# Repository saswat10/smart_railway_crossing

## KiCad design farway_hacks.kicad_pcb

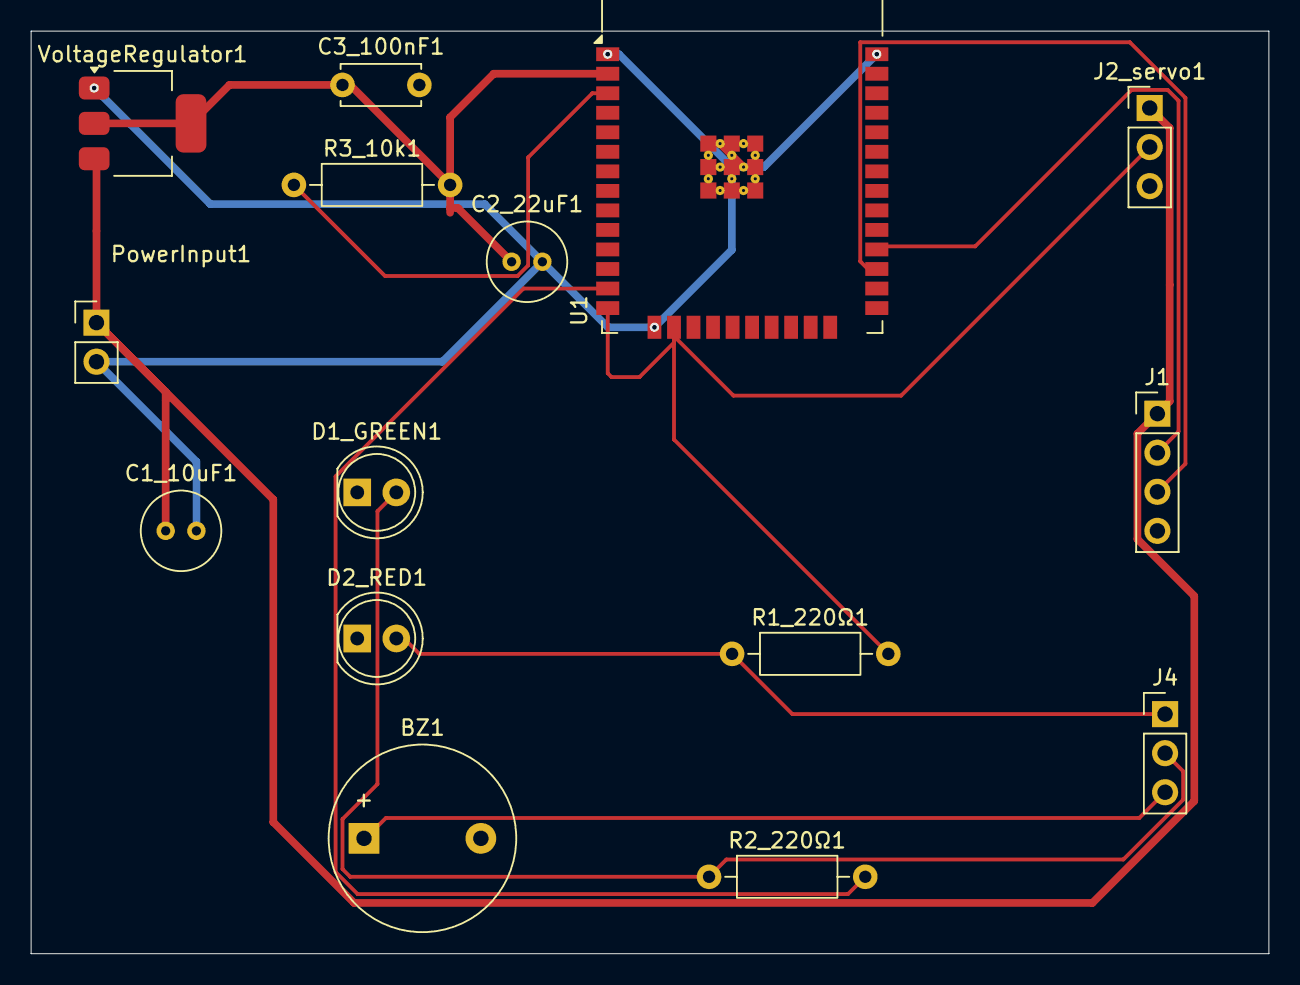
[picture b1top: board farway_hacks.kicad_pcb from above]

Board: 2 copper layers, 80.5 x 60.0 mm, 15 parts (0 on the bottom side), 11 nets.

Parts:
BZ1: Buzzer; Buzzer_12x9.5RM7.6
C1_10uF1, C2_22uF1: 52; C_Radial_D5.0mm_H5.0mm_P2.00mm
C3_100nF1: 52; C_Disc_D5.0mm_W2.5mm_P5.00mm
D1_GREEN1, D2_RED1: LED; LED_D5.0mm
J1: Conn_01x04; PinHeader_1x04_P2.54mm_Vertical
J2_servo1, J4: Conn_01x03; PinHeader_1x03_P2.54mm_Vertical
PowerInput1: Conn_01x02; PinHeader_1x02_P2.54mm_Vertical
R1_220Ω1, R2_220Ω1, R3_10k1: R; R_Axial_DIN0207_L6.3mm_D2.5mm_P10.16mm_Horizontal
U1: ESP32-WROOM-32
VoltageRegulator1: AMS1117-3.3; SOT-223-3_TabPin2

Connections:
+3V3: C2_22uF1.1, C3_100nF1.1, R3_10k1.2, U1.2 (VDD), VoltageRegulator1.2 (VO)
+5V: C1_10uF1.1, J1.1, J2_servo1.1, PowerInput1.1, VoltageRegulator1.3 (VI)
GND: BZ1.2 (-), C1_10uF1.2, C2_22uF1.2, C3_100nF1.2, D1_GREEN1.1 (K), D2_RED1.1 (K), J1.4, J2_servo1.3, PowerInput1.2, U1.1 (GND), U1.15 (GND), U1.38 (GND), U1.39 (GND), VoltageRegulator1.1 (GND)
unnamed: BZ1.1 (+), J4.3
unnamed: D1_GREEN1.2 (A), J4.2, R2_220Ω1.1
unnamed: D2_RED1.2 (A), J4.1, R1_220Ω1.1
unnamed: J1.2, U1.28 (IO17)
unnamed: J1.3, U1.27 (IO16)
unnamed: J2_servo1.2, R1_220Ω1.2, U1.14 (IO12), U1.16 (IO13)
unnamed: R3_10k1.1, U1.3 (EN)
unnamed: R2_220Ω1.2, U1.13 (IO14)

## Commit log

2026-06-09 add kicad design files
2026-06-11 Updated schematics and pcb editor
2026-06-12 Wokwi prj files
2026-06-13 updated PCB editor in KiCAD
2026-06-14 update wokwi files
2026-06-14 add frontend files
2026-06-14 add hardware docs
